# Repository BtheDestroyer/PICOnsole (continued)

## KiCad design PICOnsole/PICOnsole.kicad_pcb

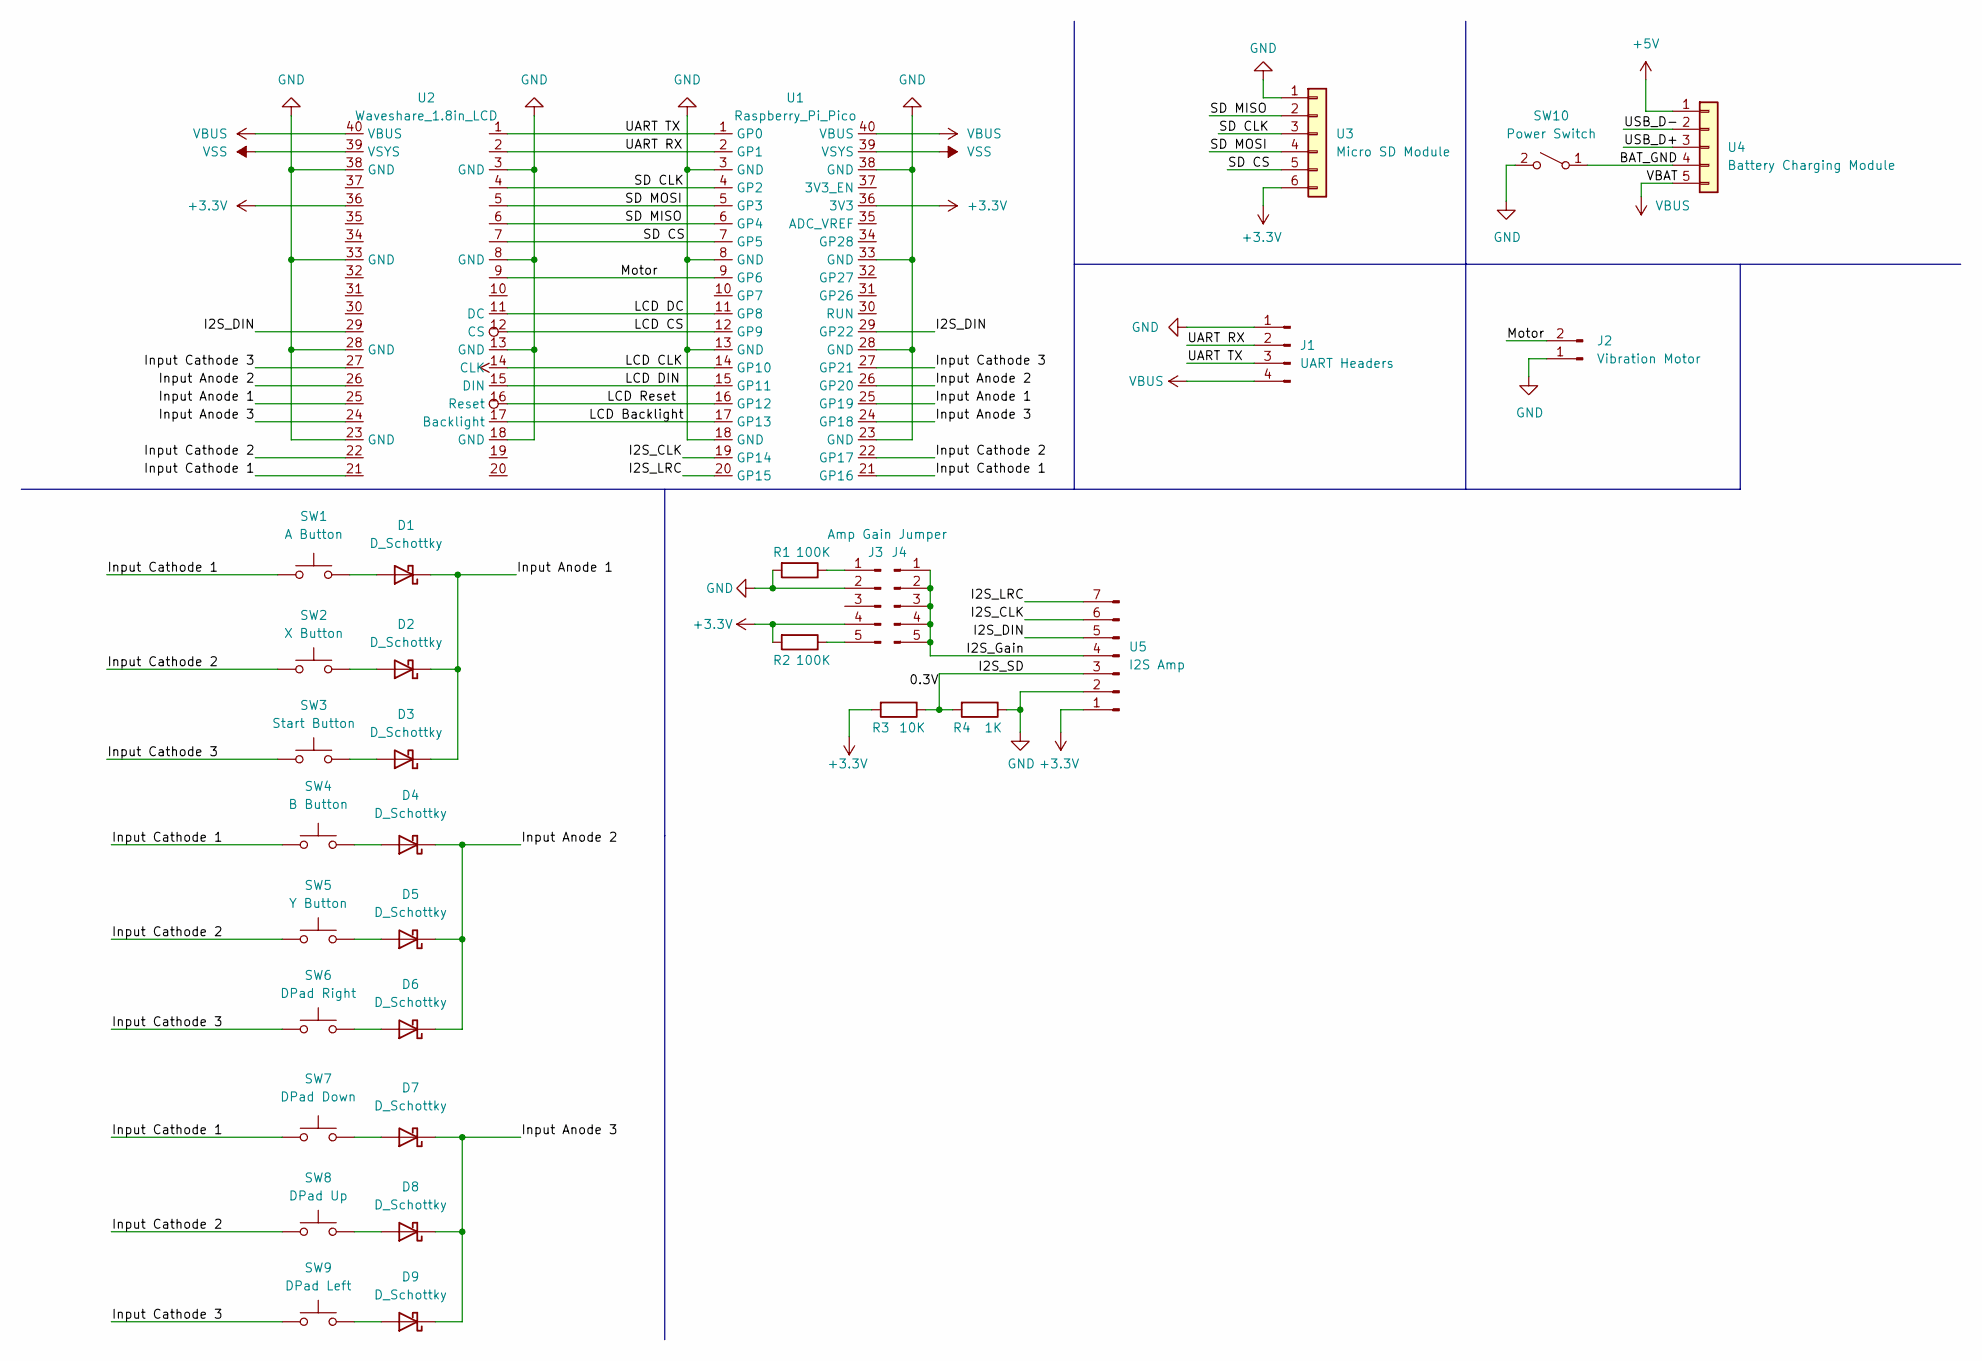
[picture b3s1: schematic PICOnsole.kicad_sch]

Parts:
D1, D2, D3, D4, D5, D6, D7, D8, D9: D_Schottky; D_A-405_P10.16mm_Horizontal
J1: UART Headers; PinHeader_1x04_P2.54mm_Vertical
J2: Vibration Motor; PinHeader_1x02_P2.54mm_Vertical
J3: Amp Gain Jumper; PinHeader_1x05_P2.54mm_Vertical
J4: Amp Gain Jumper2; PinHeader_1x05_P2.54mm_Vertical
R1, R2: 100K; R_0805_2012Metric_Pad1.20x1.40mm_HandSolder
R3: 10K; R_0805_2012Metric_Pad1.20x1.40mm_HandSolder
R4: 1K; R_0805_2012Metric_Pad1.20x1.40mm_HandSolder
SW1: A Button; SW_PUSH-12mm
SW2: X Button; SW_PUSH-12mm
SW3: Start Button; SW_PUSH_6mm
SW4: B Button; SW_PUSH-12mm
SW5: Y Button; SW_PUSH-12mm
SW6: DPad Right; SW_PUSH-12mm
SW7: DPad Down; SW_PUSH-12mm
SW8: DPad Up; SW_PUSH-12mm
SW9: DPad Left; SW_PUSH-12mm
SW10: Power Switch; PinHeader_1x03_P2.54mm_Vertical
U1: Raspberry_Pi_Pico
U2: Waveshare_1.8in_LCD
U3: Micro SD Module; PinHeader_1x06_P2.54mm_Vertical
U4: Battery Charging Module; PinHeader_1x05_P2.54mm_Vertical
U5: I2S Amp; PinHeader_1x07_P2.54mm_Vertical

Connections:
+3V3: J3.4, R2.2, R3.2, U1.36 (3V3), U2.36, U3.6, U5.1
+5V: U4.1
/0.3V: R3.1, R4.2, U5.3
/BAT_GND: SW10.1 (A), U4.4
/I2S_CLK: U1.19 (GP14), U5.6
/I2S_DIN: U1.29 (GP22), U2.29, U5.5
/I2S_Gain: J4.1, J4.2, J4.3, J4.4, J4.5, U5.4
/I2S_LRC: U1.20 (GP15), U5.7
/Input Anode 1: D1.1 (K), D2.1 (K), D3.1 (K), U1.25 (GP19), U2.25
/Input Anode 2: D4.1 (K), D5.1 (K), D6.1 (K), U1.26 (GP20), U2.26
/Input Anode 3: D7.1 (K), D8.1 (K), D9.1 (K), U1.24 (GP18), U2.24
/Input Cathode 1: SW1.1, SW4.1, SW7.1, U1.21 (GP16), U2.21
/Input Cathode 2: SW2.1, SW5.1, SW8.1, U1.22 (GP17), U2.22
/Input Cathode 3: SW3.1, SW6.1, SW9.1, U1.27 (GP22), U2.27
/LCD Backlight: U1.17 (GP13), U2.17 (Backlight)
/LCD CLK: U1.14 (GP10), U2.14 (CLK)
/LCD CS: U1.12 (GP9), U2.12 (CS)
/LCD DC: U1.11 (GP8), U2.11 (DC)
/LCD DIN: U1.15 (GP11), U2.15 (DIN)
/LCD Reset: U1.16 (GP12), U2.16 (Reset)
/Motor: J2.2, U1.9 (GP6), U2.9
/SD CLK: U1.4 (GP2), U2.4, U3.3
/SD CS: U1.7 (GP5), U2.7, U3.5
/SD MISO: U1.6 (GP4), U2.6, U3.2
/SD MOSI: U1.5 (GP3), U2.5, U3.4
/UART RX: J1.2, U1.2 (GP1), U2.2
/UART TX: J1.3, U1.1 (GP0), U2.1
/USB_D+: U4.3
/USB_D-: U4.2
GND: J1.1, J2.1, J3.2, R1.2, R4.1, SW10.2 (B), U1.3 (GND), U1.8 (GND), U1.13 (GND), U1.18 (GND), U1.23 (GND), U1.28 (GND), U1.33 (GND), U1.38 (GND), U2.3 (GND), U2.8 (GND), U2.13 (GND), U2.18 (GND), U2.23 (GND), U2.28 (GND), U2.33 (GND), U2.38 (GND), U3.1, U5.2
unnamed: D1.2 (A), SW1.2
unnamed: D2.2 (A), SW2.2
unnamed: D3.2 (A), SW3.2
unnamed: D4.2 (A), SW4.2
unnamed: D5.2 (A), SW5.2
unnamed: D6.2 (A), SW6.2
unnamed: D7.2 (A), SW7.2
unnamed: D8.2 (A), SW8.2
unnamed: D9.2 (A), SW9.2
unnamed: J3.1, R1.1
unnamed: J3.5, R2.1
VBUS: J1.4, U1.40 (VBUS), U2.40 (VBUS), U4.5
VSS: U1.39 (VSYS), U2.39 (VSYS)

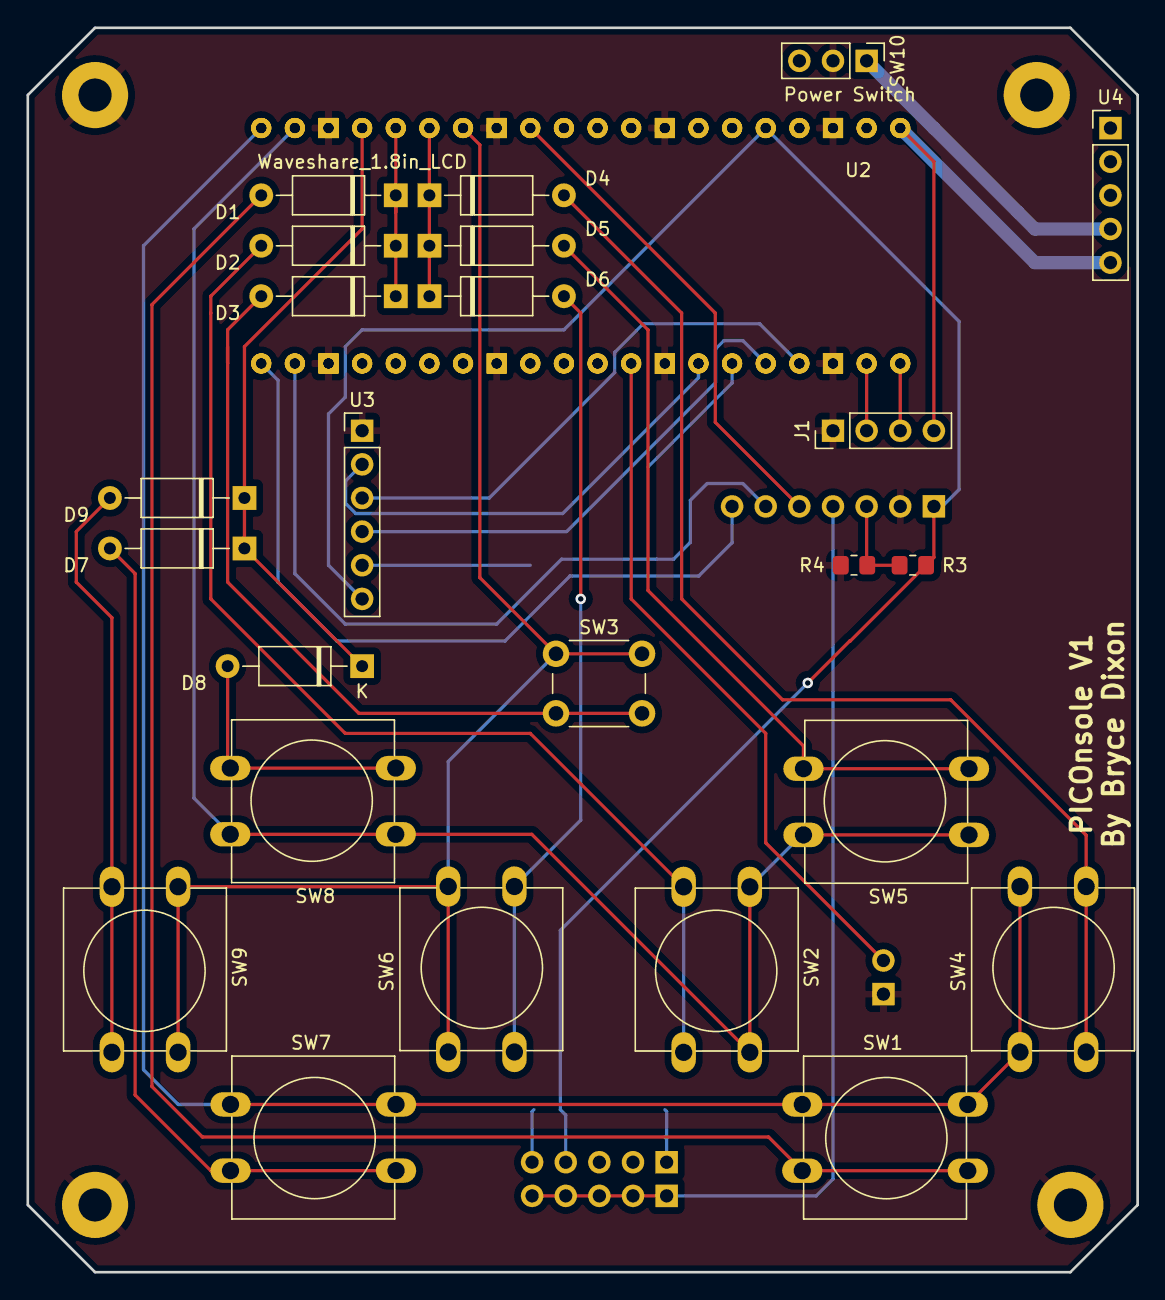
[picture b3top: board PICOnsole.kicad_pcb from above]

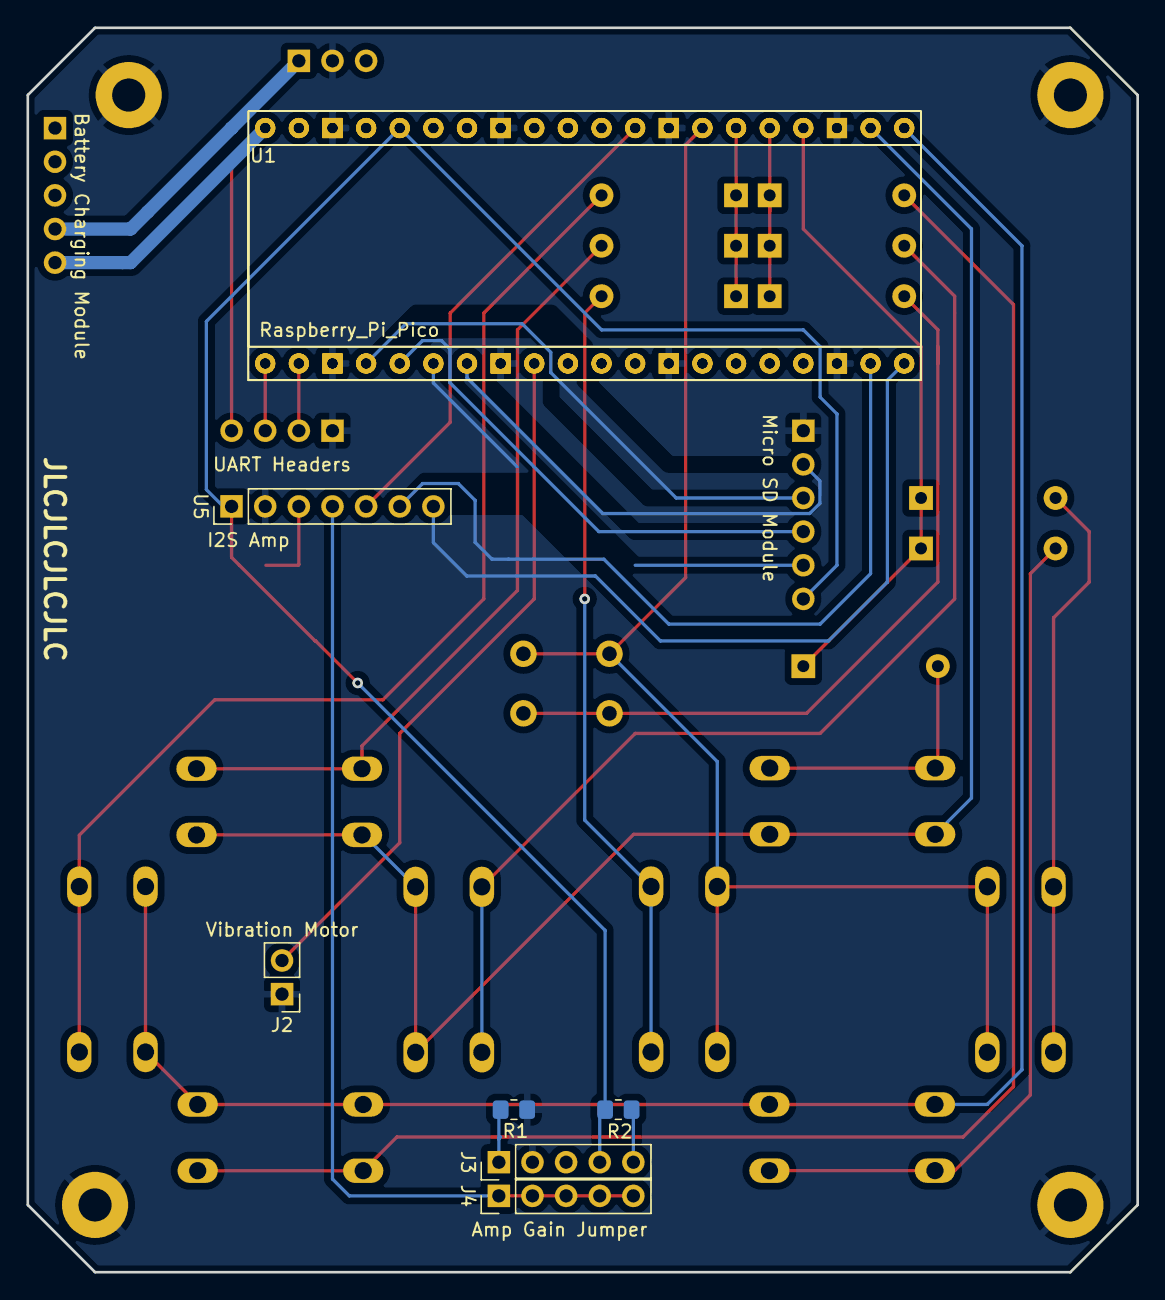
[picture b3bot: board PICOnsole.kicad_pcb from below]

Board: 2 copper layers, 83.8 x 94.0 mm, 32 parts (8 on the bottom side), 40 nets.

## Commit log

2023-02-04 Proof of concept stage
2023-02-04 SD card read/write support
2023-02-05 Added memory management; Need to come back later and make a linker script to automate hardcoded addresses
2023-02-06 REMOVED Memory Manager in favor of explicit memory regions provided by the linker
2023-02-06 Example program compiles with special segments for OS interaction; OS can now read ELF headers from SD card
2023-02-06 ELF Segment Headers are now iterated over
2023-02-06 Reading segments from ELF on SD
2023-02-07 Loading and launching ELF correctly, but calling libc functions results in a hardfault...
2023-03-12 Program is loaded and launched from SD card
2023-03-15 Program is now launched on core1
2023-03-22 Started work on Audio Speaker+Vibration motor; Started PCB design
2023-03-24 temp
2023-03-24 rm temp
2023-03-25 Sped up ELF loading by only erasing the necessary segments of flash; added Pi4/00 variants of debugging config
2023-03-26 Added text drawing and 5px font; File reorganization
2023-03-26 Test program now draws text
2023-03-26 Buttons/input now functional. Added input_test program
2023-04-06 Updated CAD files
2023-04-07 Moving off Pi400
2023-04-07 Increased OS RAM size to allow for better errors. Currently programs can't find builtin functions (eg memset) correctly
2023-10-20 Moved KiCad files to KiCad folder; Started new revision of project with 2 Picos
2023-11-23 Updated KiCad to V1.1.2
